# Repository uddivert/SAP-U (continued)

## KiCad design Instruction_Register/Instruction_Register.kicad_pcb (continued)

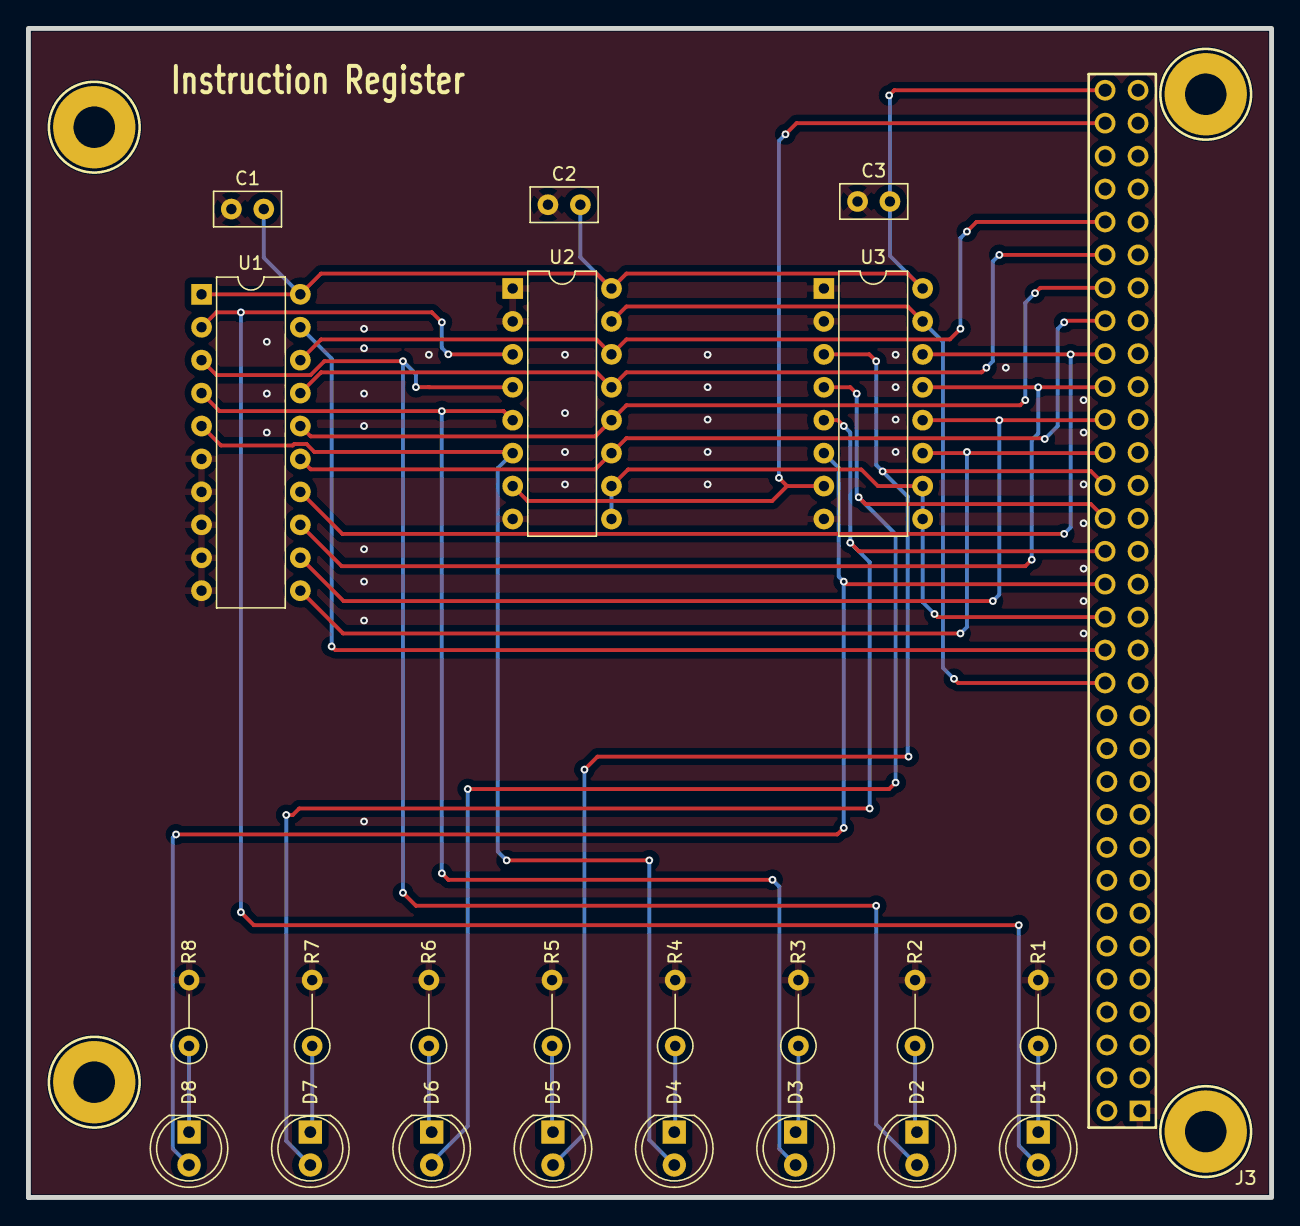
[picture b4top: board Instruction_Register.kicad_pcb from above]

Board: 2 copper layers, 95.9 x 90.2 mm, 23 parts (0 on the bottom side), 30 nets.

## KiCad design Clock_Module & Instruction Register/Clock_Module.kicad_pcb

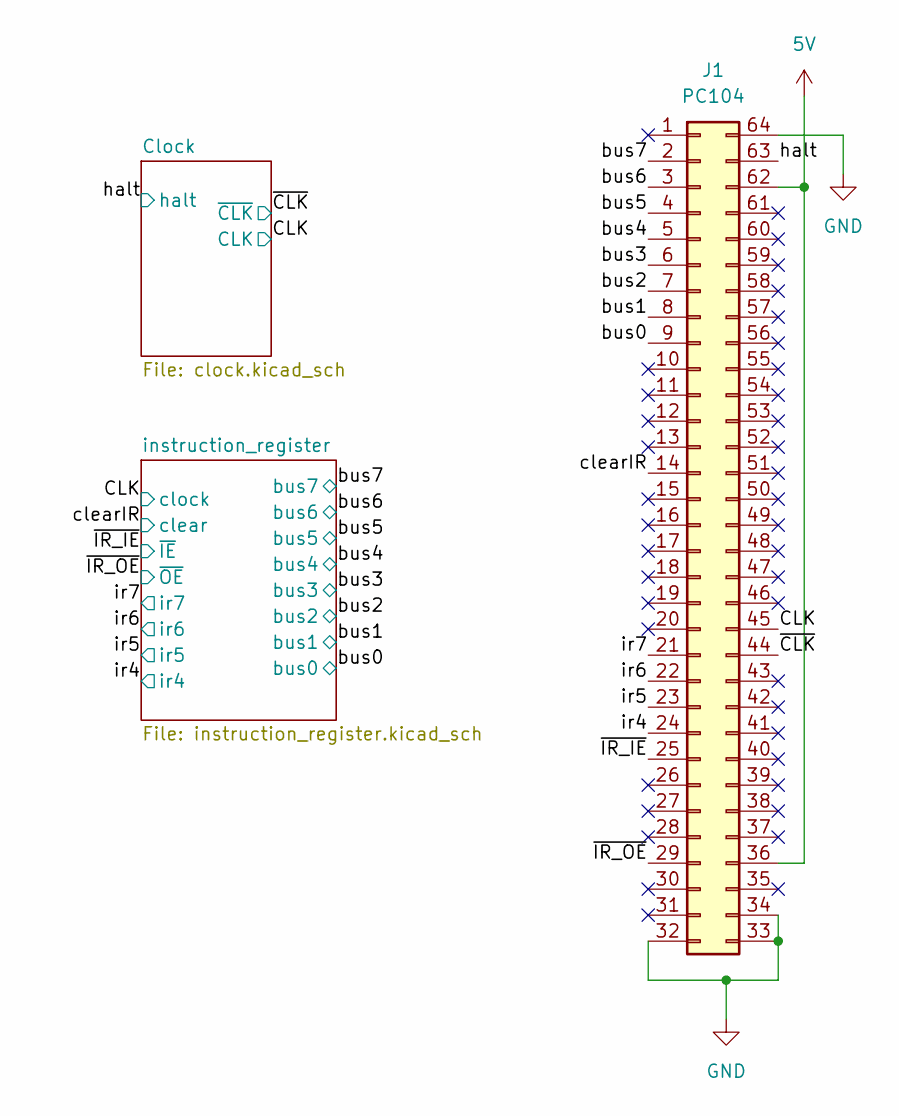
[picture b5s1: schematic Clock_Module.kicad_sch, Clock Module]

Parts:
J1: PC104; PinSocket_2x32_P2.54mm_Vertical

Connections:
5V: J1.36, J1.62; also elsewhere on the board
/CLK: J1.45; also elsewhere on the board
/bus0: J1.9; also elsewhere on the board
/bus1: J1.8; also elsewhere on the board
/bus2: J1.7; also elsewhere on the board
/bus3: J1.6; also elsewhere on the board
/bus4: J1.5; also elsewhere on the board
/bus5: J1.4; also elsewhere on the board
/bus6: J1.3; also elsewhere on the board
/bus7: J1.2; also elsewhere on the board
/clearIR: J1.14; also elsewhere on the board
/halt: J1.63; also elsewhere on the board
/ir4: J1.24; also elsewhere on the board
/ir5: J1.23; also elsewhere on the board
/ir6: J1.22; also elsewhere on the board
/ir7: J1.21; also elsewhere on the board
/~CLK: J1.44; also elsewhere on the board
/~IR_IE: J1.25; also elsewhere on the board
/~IR_OE: J1.29; also elsewhere on the board
GND: J1.32, J1.33, J1.34, J1.64; also elsewhere on the board

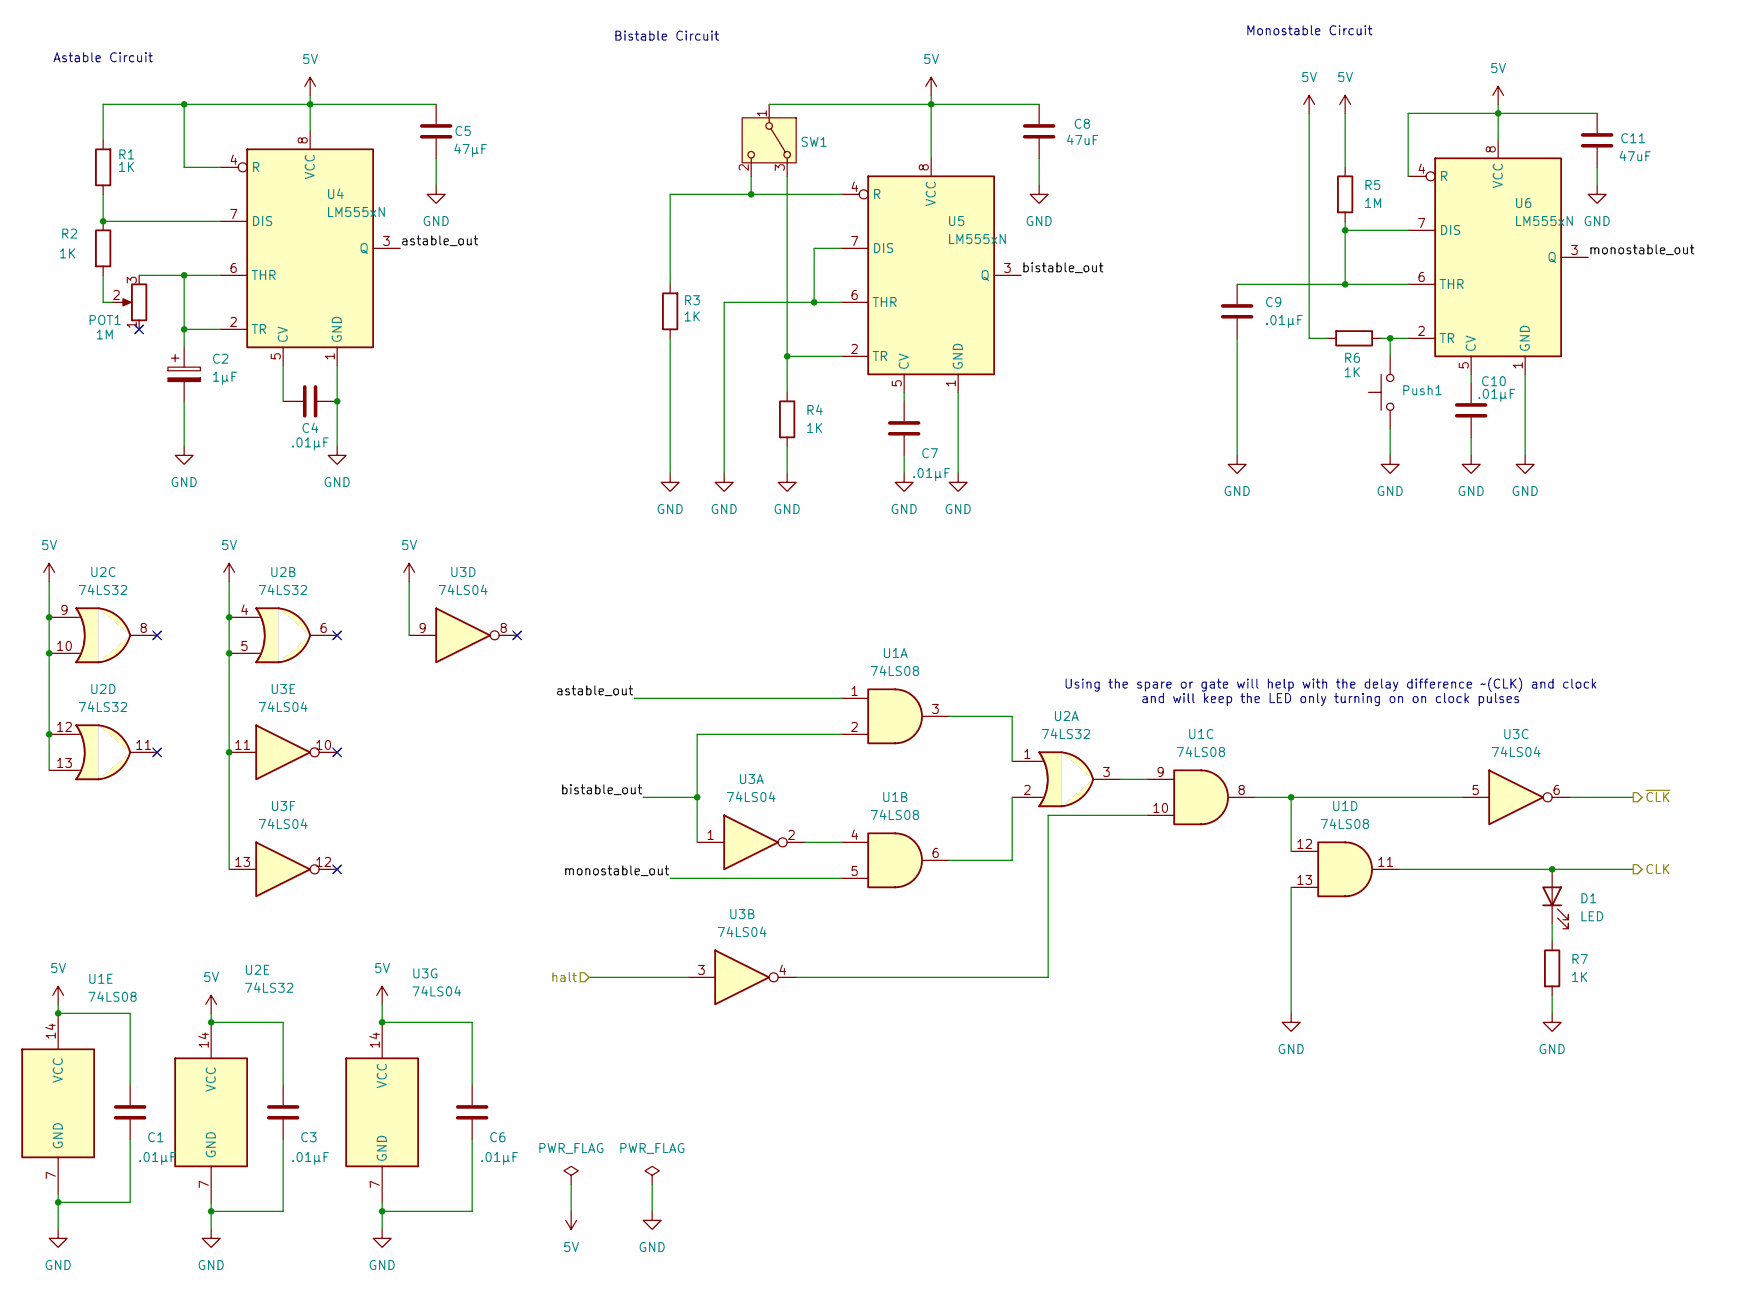
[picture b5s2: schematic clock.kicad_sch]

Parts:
C1, C3, C4, C6, C7, C9, C10: .01µF; C_Disc_D5.0mm_W2.5mm_P2.50mm
C2: 1µF; C_Radial_D5.0mm_H11.0mm_P2.00mm
C5: 47µF; C_Disc_D5.0mm_W2.5mm_P2.50mm
C8, C11: 47uF; C_Disc_D5.0mm_W2.5mm_P2.50mm
D1: LED; LED_D5.0mm
POT1: 1M; Potentiometer_Bourns_3386F_Vertical
Push1: SW_Push; SW_PUSH_6mm_H4.3mm
R1, R2, R3, R4, R6, R7: 1K; R_Axial_DIN0207_L6.3mm_D2.5mm_P5.08mm_Vertical
R5: 1M; R_Axial_DIN0207_L6.3mm_D2.5mm_P5.08mm_Vertical
SW1: Switch; SW_Slide-Jameco-SS-12E17-G020
U1: 74LS08; SN74LS08N
U2: 74LS32; SN74LS32N
U3: 74LS04; SN74LS04N
U4, U5, U6: LM555xN; DIP-8_W7.62mm

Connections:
5V: C1.2, C3.2, C5.1, C6.2, C8.2, C11.1, R1.2, R5.1, R6.2, SW1.1 (B), U1.14 (VCC), U2.4, U2.5, U2.9, U2.10, U2.12, U2.13, U2.14 (VCC), U3.9, U3.11, U3.13, U3.14 (VCC), U4.4 (R), U4.8 (VCC), U5.8 (VCC), U6.4 (R), U6.8 (VCC); also elsewhere on the board
/CLK: D1.2 (A), U1.11; also elsewhere on the board
/Clock/astable_out: U1.1, U4.3 (Q)
/Clock/bistable_out: U1.2, U3.1, U5.3 (Q)
/Clock/monostable_out: U1.5, U6.3 (Q)
/halt: U3.3; also elsewhere on the board
/~CLK: U3.6; also elsewhere on the board
GND: C1.1, C2.2, C3.1, C4.1, C5.2, C6.1, C7.1, C8.1, C9.1, C10.1, C11.2, Push1.1, R3.1, R4.2, R7.2, U1.7 (GND), U1.13, U2.7 (GND), U3.7 (GND), U4.1 (GND), U5.1 (GND), U5.6 (THR), U5.7 (DIS), U6.1 (GND); also elsewhere on the board
unnamed: D1.1 (K), R7.1
unnamed: POT1.2, R2.2
unnamed: R4.1, SW1.3 (A), U5.2 (TR)
unnamed: R3.2, SW1.2 (C), U5.4 (R)
unnamed: U1.3, U2.1
unnamed: U1.4, U3.2
unnamed: U1.6, U2.2
unnamed: U1.9, U2.3
unnamed: U1.10, U3.4
unnamed: U1.8, U1.12, U3.5
unnamed: C4.2, U4.5 (CV)
unnamed: R1.1, R2.1, U4.7 (DIS)
unnamed: C2.1, POT1.3, U4.2 (TR), U4.6 (THR)
unnamed: C7.2, U5.5 (CV)
unnamed: C10.2, U6.5 (CV)
unnamed: C9.2, R5.2, U6.6 (THR), U6.7 (DIS)
unnamed: Push1.2, R6.1, U6.2 (TR)

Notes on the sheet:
Astable Circuit
Bistable Circuit
Monostable Circuit
Using the spare or gate will help with the delay difference ~(CLK) and clock and will keep the LED only turning on on clock pulses

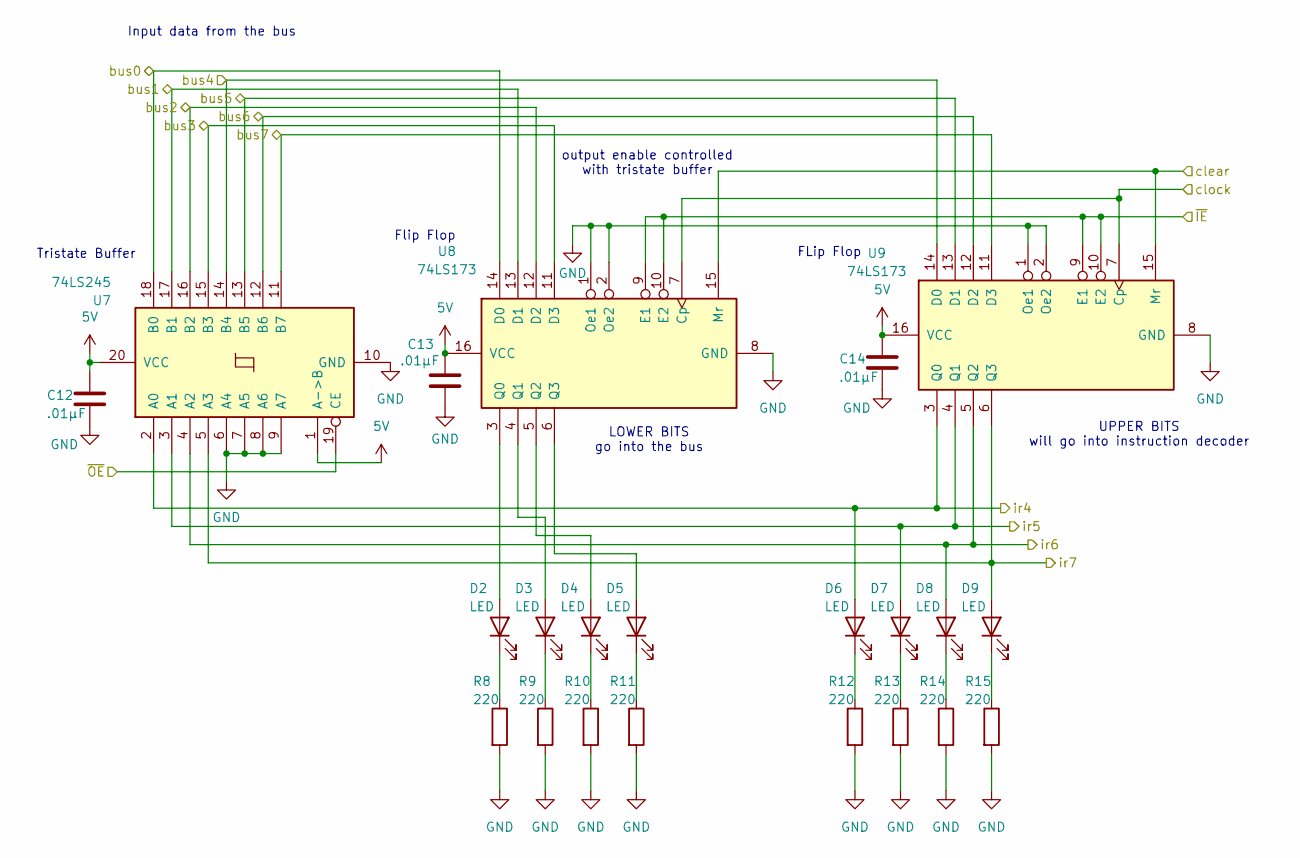
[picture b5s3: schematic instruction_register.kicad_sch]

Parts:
C12, C13, C14: .01µF; C_Disc_D5.0mm_W2.5mm_P2.50mm
D2, D3, D4, D5, D6, D7, D8, D9: LED; LED_D5.0mm
R8, R9, R10, R11, R12, R13, R14, R15: 220; R_Axial_DIN0207_L6.3mm_D2.5mm_P5.08mm_Vertical
U7: 74LS245; DIP-20_W7.62mm
U8, U9: 74LS173; DIP-16_W7.62mm

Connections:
5V: C12.2, C13.2, C14.2, U7.1 (A->B), U7.20 (VCC), U8.16 (VCC), U9.16 (VCC); also elsewhere on the board
/CLK: U8.7 (Cp), U9.7 (Cp); also elsewhere on the board
/bus0: U7.18 (B0), U8.14 (D0); also elsewhere on the board
/bus1: U7.17 (B1), U8.13 (D1); also elsewhere on the board
/bus2: U7.16 (B2), U8.12 (D2); also elsewhere on the board
/bus3: U7.15 (B3), U8.11 (D3); also elsewhere on the board
/bus4: U7.14 (B4), U9.14 (D0); also elsewhere on the board
/bus5: U7.13 (B5), U9.13 (D1); also elsewhere on the board
/bus6: U7.12 (B6), U9.12 (D2); also elsewhere on the board
/bus7: U7.11 (B7), U9.11 (D3); also elsewhere on the board
/clearIR: U8.15 (Mr), U9.15 (Mr); also elsewhere on the board
/ir4: D6.2 (A), U7.2 (A0), U9.3 (Q0); also elsewhere on the board
/ir5: D7.2 (A), U7.3 (A1), U9.4 (Q1); also elsewhere on the board
/ir6: D8.2 (A), U7.4 (A2), U9.5 (Q2); also elsewhere on the board
/ir7: D9.2 (A), U7.5 (A3), U9.6 (Q3); also elsewhere on the board
/~IR_IE: U8.9 (E1), U8.10 (E2), U9.9 (E1), U9.10 (E2); also elsewhere on the board
/~IR_OE: U7.19 (CE); also elsewhere on the board
GND: C12.1, C13.1, C14.1, R8.2, R9.2, R10.2, R11.2, R12.2, R13.2, R14.2, R15.2, U7.6 (A4), U7.7 (A5), U7.8 (A6), U7.9 (A7), U7.10 (GND), U8.1 (Oe1), U8.2 (Oe2), U8.8 (GND), U9.1 (Oe1), U9.2 (Oe2), U9.8 (GND); also elsewhere on the board
unnamed: D2.2 (A), U8.3 (Q0)
unnamed: D2.1 (K), R8.1
unnamed: D3.2 (A), U8.4 (Q1)
unnamed: D3.1 (K), R9.1
unnamed: D4.2 (A), U8.5 (Q2)
unnamed: D4.1 (K), R10.1
unnamed: D5.2 (A), U8.6 (Q3)
unnamed: D5.1 (K), R11.1
unnamed: D6.1 (K), R12.1
unnamed: D7.1 (K), R13.1
unnamed: D8.1 (K), R14.1
unnamed: D9.1 (K), R15.1

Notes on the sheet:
UPPER BITS will go into instruction decoder
Flip Flop
FLip Flop
output enable controlled with tristate buffer
LOWER BITS go into the bus
Input data from the bus
Tristate Buffer

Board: 2 copper layers, 55 parts (0 on the bottom side), 52 nets, no tracks yet.

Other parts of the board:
M_1, M_2, M_3, M_4: MountingHole_2.5mm_Pad

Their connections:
GND: M_1.1, M_2.1, M_3.1, M_4.1; also elsewhere on the board

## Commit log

2024-09-17 first commit: added wiki and project files
2024-09-18 Checkpoint: created documentation and schematic for the astable portion of the clock module
2024-09-22 added circuit for monostable clock
2024-09-23 Checkpoint: added circuit for Bistable
2024-09-24 Checkpoint: added switching logic
2024-10-01 Checkpoint: moved simulations to new kicad project
2024-10-02 Checkpoint: fixed ERC errors
2024-10-02 cleaned up circuit for bistable, monostable, and astable circuits
2024-10-03 Checkpoint: completed schematic for Clock Module
2024-10-03 Checkpoint: Linked footprints to schematics
2024-10-08 Checkpoint: added 555 timer simulation library
2024-10-08 Checkpoint: removed simulation, cleaned up schematic
2024-10-09 Checkpoint: cleaned up clock module. Made one schematic. Good stop point
2024-10-09 added sr_latch simulation
2024-10-13 Checkpoint: added d_latch and simulation
2024-10-13 created d_flip flop test and simulation
2024-10-13 Checkpoint: formatting and renamed signals
2024-10-15 updated formatter
2024-10-16 Checkpoint: Added reset to d_flip_flop and updated testbench
2024-10-17 added reset, fixed time scale, fixed 1 bit register
2024-10-17 fixed formatting
2024-10-17 Checkpoint: more complete sn54173 model
2024-10-17 Update sn54173_quad_flip_flop.v
    Cleaned comments in code
2024-10-17 Checkpoint: used generate and modified test bench
2024-10-18 completed sn54173 simulation
2024-10-20 added register and register_tb
2024-10-20 add instruction register and instruction register test
2024-10-20 removing workflows
2024-10-20 added quartus files
2024-10-21 Updated Schematic to PC104 standards, updated Simulation for intel-quartus, updated PCB constraints, and edited board layout
2024-10-22 partially complete pcb and updated schematic with bypass capacitors
2024-10-23 Routed PCB
2024-10-30 completed clock module
2024-11-08 added more descriptive comments
2024-11-12 Added boilerplate for ALU
2024-11-12 added A, B, and Instructional Regsiters
2024-11-14 updated wiki, created board outline for alu, made registers with hierarchical label
2024-11-20 added templates for the dm74ls283
2024-11-22 added full adder with test bench and wiki updates
2024-11-23 added adder and test code
2024-11-23 fixed variables in dm74ls283 and added alu logic
2024-11-23 fixing ALU testbench
2024-11-24 updated tests, fixed alu
2024-11-24 wire top module and added testbench
2024-11-24 fixed register schematic
2024-11-25 completed alu schematic with errors
2024-11-26 removed buses and replaced with hierarchical labels
2024-11-27 added instructional register
2024-11-28 added flags
2024-12-08 fixed incorrect footprint for sn54173
2024-12-09 fixed wiring issues
2024-12-09 added bypass capacitors
2024-12-09 preliminary board layout, will move IR to clock module
2024-12-10 layed out PCB
2024-12-11 added flag register to alu.v
2024-12-12 fixed flags register
2024-12-22 updated testbench
2024-12-26 Placed clock module again
2024-12-27 Updated Clock Module Schematic, and moved Instruction Register to new board
2024-12-29 mostly routed IR, fixed logic issue in Clock Module
2025-01-01 returning to pc104 standard
2025-01-03 fixed clock module, made it back into pc104 board standard
2025-01-04 updated instruction register to match pc104
2025-01-04 updated Sim files
2025-02-03 updated registers and alu
2025-02-11 placeholder files for new Simulation structure
2025-02-12 created test module for common hdl components
2025-02-13 updated Makefile, and added tests for dff, and dlatch
2025-02-13 added new tests for d_latch and d_flip flop using cocotb
2025-02-20 added sr_latch test
2025-02-20 added full_adder test
2025-02-20 added tests for dm74ls283_quad_adder
2025-02-23 updated tests
2025-02-23 all tests have been updated to be individual testbenches
2025-02-24 updated formatting
2025-02-25 added f189 ram module and testbench
2025-02-26 RAM module build - part 1 complete
2025-02-26 Added sn74ls159 module and test
2025-02-26 Added memory address register
2025-02-27 fixed sn74ls159 testbench, linting, and formatting
2025-02-27 added memory address register and memory address register testbench
2025-03-11 ram checkpoint
2025-03-13 filled out ram module
2025-03-20 fixed incorrect module name
2025-03-25 updated ram design
2025-03-26 fixed memory_tb.v
2025-03-26 fixed ram compilation issue
2025-03-26 added ram testbench.. Doesn't work...
2025-03-27 added ram padding
2025-03-29 updated makefile
2025-03-31 working on ram still
2025-03-31 fixed ram not using correct signal
2025-03-31 added comments. Still fixing ram
2025-04-01 fixed ram inverting output error
2025-04-01 fixed memory testbench
2025-04-01 updated ram_tb
2025-04-01 work in progress
2025-04-02 temporary fix to f189 module so it is async. Need to rewrite properly without always @ block
2025-04-03 updated ram_tb, updated formatting
2025-04-03 formatting
2025-04-07 added register for ram
2025-04-08 made f189.v asynchronous
2025-04-09 fixed f189.v
2025-04-09 fixed memory
2025-05-05 removed mar
2025-05-27 ram working - i think
2025-05-29 rewriting ram
2025-05-29 updated testbench for ram
2025-06-01 debugging with SAP_U testbench
2025-06-02 sim going through major revisions
2025-06-08 added Databus Manager
2025-06-09 added enables to Bus Manager. Need to fix ram. Can write to bus with ALU
2025-06-09 updated ram_module signals
2025-06-09 control logic not working again
2025-06-09 fixed control signal in ram
2025-06-10 formatting, ram prints to bus
2025-06-23 updated common_tb.v
2025-06-23 updated ram test... need to verify
2025-06-23 updated variable names
2025-07-22 added cap's between power pins
2025-07-26 updated Arithemetic Logic Unit
2025-07-26 Removed Register schematic from ALU & created Memory Address Register
2025-07-29 added buses for addresses. RAM WIP
2025-07-30 connected internal memory
2025-07-31 updated RAM, changed bus alignment in ALU, RAM, and registers
2025-08-01 connected RAM
2025-08-04 fixed Ram register, fixed mar in ram.v, updated caps in alu, ram, and instruction register
2025-08-05 made jk_flip_flop.v
2025-08-05 need to fix and add master_slave jkff
2025-08-06 added jk_flip_flop and dm7476
2025-08-12 added sn54161 program counter
2025-08-22 Added Program Counter Module
2025-08-24 add program_counter
2025-08-24 added Top level test bench
2025-08-26 formatting, linting, and fixed bus for program counter in SAP_U_tb.v
2025-08-26 Added Program Counter Schematic
2025-09-03 added programmer code for eeprom
2025-09-07 added verilog for 7 segment display
2025-09-08 added dm74ls139 decoder
2025-09-08 added seven segment display
2025-09-11 added 7 segment display to display module
2025-09-15 updated display to properly use 3 segments
2025-10-01 Added 28C16 Rom module
2025-10-18 WIP updated ROM
2025-10-20 fixed jk flip flop to be dual jk flip flop
